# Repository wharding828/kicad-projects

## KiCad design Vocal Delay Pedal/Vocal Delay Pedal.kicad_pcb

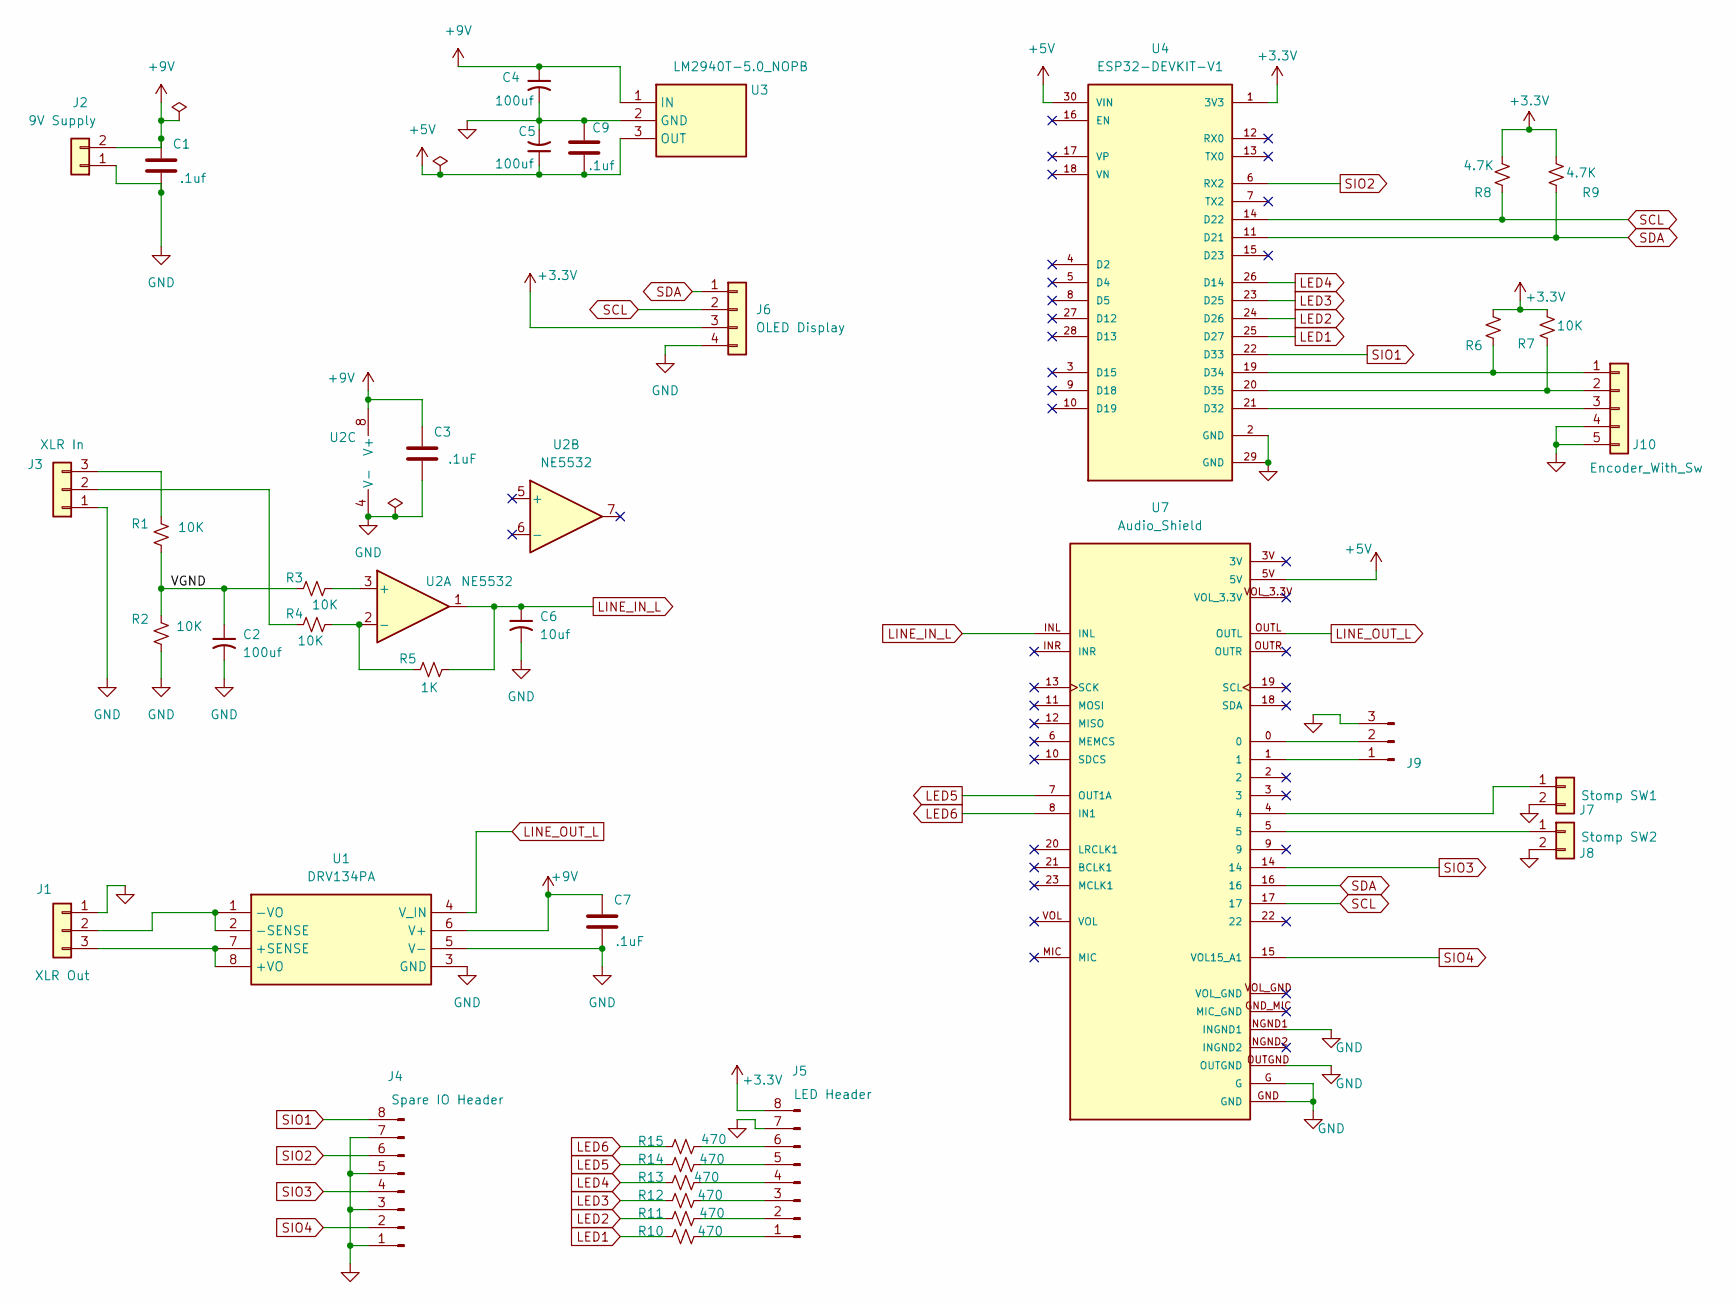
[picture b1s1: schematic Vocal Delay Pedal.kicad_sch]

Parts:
C1, C9: .1uf; C_Disc_D3.0mm_W1.6mm_P2.50mm
C2, C4, C5: 100uf; C_Radial_D5.0mm_H5.0mm_P2.00mm
C3, C7: .1uF; C_Disc_D3.0mm_W1.6mm_P2.50mm
C6: 10uf; C_Radial_D5.0mm_H5.0mm_P2.00mm
J1: XLR Out; JST_XH_B3B-XH-A_1x03_P2.50mm_Vertical
J2: 9V Supply; JST_XH_B2B-XH-A_1x02_P2.50mm_Vertical
J3: XLR In; JST_XH_B3B-XH-A_1x03_P2.50mm_Vertical
J4: Spare IO Header; PinHeader_1x08_P2.54mm_Vertical
J5: LED Header; PinHeader_1x08_P2.54mm_Vertical
J6: OLED Display; JST_XH_B4B-XH-A_1x04_P2.50mm_Vertical
J7: Stomp SW1; JST_XH_B2B-XH-A_1x02_P2.50mm_Vertical
J8: Stomp SW2; JST_XH_B2B-XH-A_1x02_P2.50mm_Vertical
J9: Conn_01x03_Pin; PinHeader_1x03_P2.54mm_Vertical
J10: Encoder_With_Sw; JST_XH_B5B-XH-A_1x05_P2.50mm_Vertical
R1, R2, R3, R4, R6, R7: 10K; R_Axial_DIN0207_L6.3mm_D2.5mm_P7.62mm_Horizontal
R5: 1K; R_Axial_DIN0207_L6.3mm_D2.5mm_P7.62mm_Horizontal
R8, R9: 4.7K; R_Axial_DIN0207_L6.3mm_D2.5mm_P7.62mm_Horizontal
R10, R11, R12, R13, R14, R15: 470; R_Axial_DIN0207_L6.3mm_D2.5mm_P7.62mm_Horizontal
U1: DRV134PA; DIP794W53P254L959H508Q8N; Mouser Part Number 595-DRV134PA
U2: NE5532; DIP-8_W7.62mm
U3: LM2940T-5.0_NOPB; TO254P470X1028X1955-3P; Mouser Part Number 926-LM2940T-5.0/NOPB
U4: ESP32-DEVKIT-V1; MODULE_ESP32_DEVKIT_V1; PARTREV N/A
U7: Audio_Shield; MODULE_DEV-15845

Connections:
+3.3V: J5.8, J6.3, R6.1, R7.1, R8.1, R9.1, U4.1 (3V3)
+5V: C5.1, C9.2, U3.3 (OUT), U4.30 (VIN), U7.5V
+9V: C1.1, C3.1, C4.1, C7.1, J2.2, U1.6 (V+), U2.8 (V+), U3.1 (IN)
/VGND: C2.1, R1.2, R2.1, R3.1
GND: C1.2, C2.2, C3.2, C4.2, C5.2, C6.2, C7.2, C9.1, J1.1, J2.1, J3.1, J4.1, J4.3, J4.5, J4.7, J5.7, J6.4, J7.2, J8.2, J9.3, J10.4, J10.5, R2.2, U1.3 (GND), U1.5 (V-), U2.4 (V-), U3.2 (GND), U4.2 (GND), U4.29 (GND), U7.G, U7.GND, U7.INGND1, U7.OUTGND
LED1: R10.1, U4.25 (D27)
LED2: R11.1, U4.24 (D26)
LED3: R12.1, U4.23 (D25)
LED4: R13.1, U4.26 (D14)
LED5: R14.1, U7.7 (OUT1A)
LED6: R15.1, U7.8 (IN1)
LINE_IN_L: C6.1, R5.2, U2.1, U7.INL
LINE_OUT_L: U1.4 (V_IN), U7.OUTL
unnamed: J1.2, U1.1 (-VO), U1.2 (-SENSE)
unnamed: J1.3, U1.7 (+SENSE), U1.8 (+VO)
unnamed: J3.2, R4.1
unnamed: J3.3, R1.1
unnamed: J5.1, R10.2
unnamed: J5.2, R11.2
unnamed: J5.3, R12.2
unnamed: J5.4, R13.2
unnamed: J5.5, R14.2
unnamed: J5.6, R15.2
unnamed: J7.1, U7.4
unnamed: J8.1, U7.5
unnamed: J9.1, U7.1
unnamed: J9.2, U7.0
unnamed: J10.1, R6.2, U4.19 (D34)
unnamed: J10.2, R7.2, U4.20 (D35)
unnamed: J10.3, U4.21 (D32)
unnamed: R3.2, U2.3 (+)
unnamed: R4.2, R5.1, U2.2 (-)
SCL: J6.2, R8.2, U4.14 (D22), U7.17
SDA: J6.1, R9.2, U4.11 (D21), U7.16
SIO1: J4.8, U4.22 (D33)
SIO2: J4.6, U4.6 (RX2)
SIO3: J4.4, U7.14
SIO4: J4.2, U7.15 (VOL15_A1)

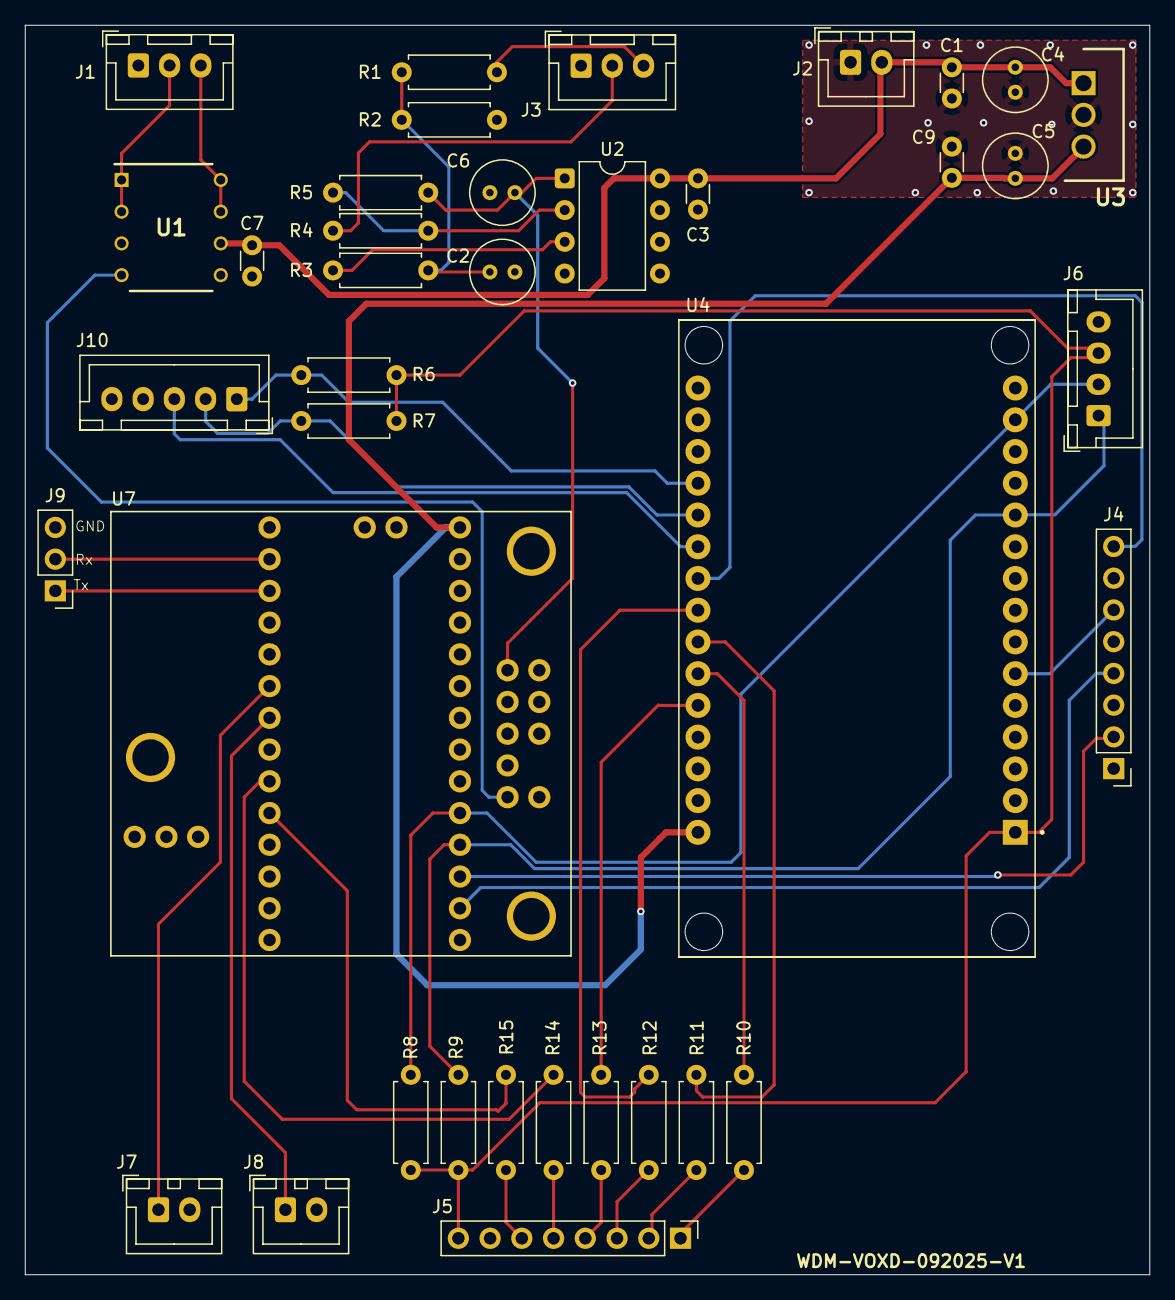
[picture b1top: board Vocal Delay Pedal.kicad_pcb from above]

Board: 2 copper layers, 90.0 x 100.0 mm, 38 parts (0 on the bottom side), 38 nets.

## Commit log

2025-10-05 Initial commit: All KiCad projects + shared libraries
2025-10-05 -Changed sheet size to 11x17
